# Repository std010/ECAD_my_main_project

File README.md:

# ECAD_my_main_project

Составлена и разведена принципиальная схема Модуля для очувствления протеза

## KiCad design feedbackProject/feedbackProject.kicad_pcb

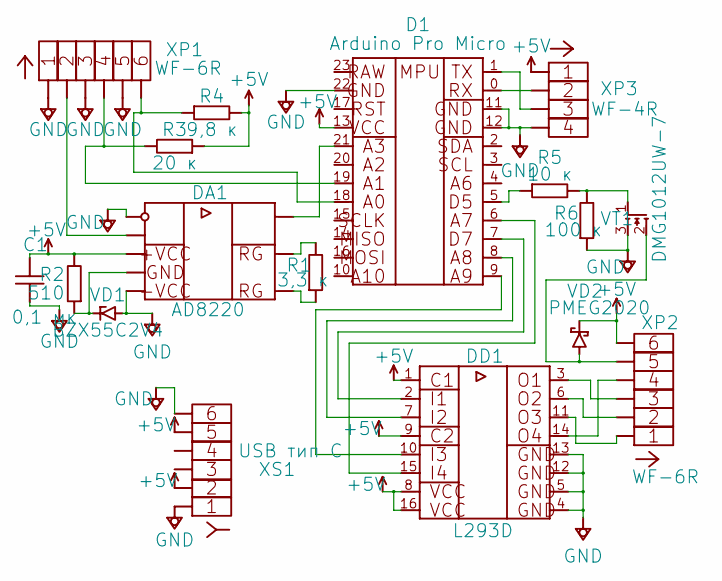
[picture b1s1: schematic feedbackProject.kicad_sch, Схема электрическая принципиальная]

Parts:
C1: 0,1 мк; capacitor_0805_Most_Density
D1: Arduino Pro Micro; proMicroSMD
DA1: AD8220; MSOP-8
DD1: L293D; PowerDIP-16
R1: 3,3 к; resistor_0805_Most_Density
R2: 510; resistor_0805_Most_Density
R3: 20 к; resistor_0805_Most_Density
R4: 9,8 к; resistor_0805_Most_Density
R5: 10 к; resistor_0805_Most_Density
R6: 100 к; resistor_0805_Most_Density
VD1: BZX55C2V4; diode_SOD-80C_Most_Density
VD2: PMEG2020; diode_SOD-323_Most_Density
VT1: DMG1012UW-7; transistor-SOT-323
XP1, XP2: WF-6R
XP3: WF-4R
XS1: USB тип C; USB-Type-C-4125-GF-A-0190

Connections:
+5V: C1.2, D1.13, DA1.8, DD1.1, DD1.8, DD1.9, DD1.16, R2.2, R3.1, R4.2, VD2.C, XP2.6, XP3.1, XS1.2, XS1.5
GND: C1.1, D1.11, D1.12, D1.22, DA1.1, DA1.5, DD1.4, DD1.5, DD1.12, DD1.13, R6.1, VD1.A, VT1.3, XP1.1, XP1.3, XP1.5, XP3.4, XS1.1, XS1.6
unnamed: D1.0, XP3.2
unnamed: D1.1, XP3.3
unnamed: D1.5, R5.1
unnamed: D1.6, DD1.15
unnamed: D1.7, DD1.2
unnamed: D1.8, DD1.7
unnamed: D1.9, DD1.10
unnamed: D1.18, R4.1, XP1.6
unnamed: D1.19, R3.2, XP1.4
unnamed: D1.21, DA1.7
unnamed: DA1.2, R1.2
unnamed: DA1.3, R1.1
unnamed: DA1.4, XP1.2
unnamed: DA1.6, R2.1, VD1.C
unnamed: DD1.3, XP2.3
unnamed: DD1.6, XP2.2
unnamed: DD1.11, XP2.1
unnamed: DD1.14, XP2.4
unnamed: R5.2, R6.2, VT1.1
unnamed: VD2.A, VT1.2, XP2.5

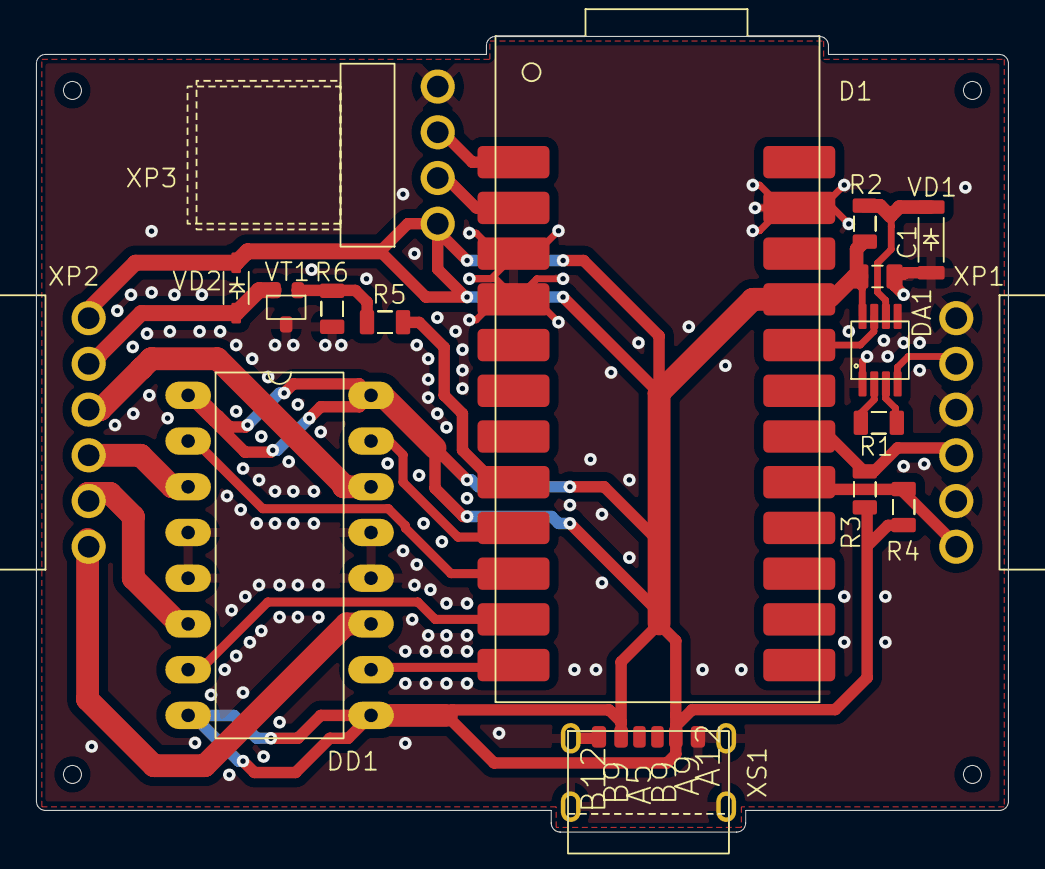
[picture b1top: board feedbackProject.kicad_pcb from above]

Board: 2 copper layers, 54.0 x 44.2 mm, 17 parts (0 on the bottom side), 22 nets.

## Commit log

2025-09-11 adding lib repo
2025-10-12 another check
2025-10-19 library update check
2025-10-20 library update check of adding Arduino pro micro footprint + minor fix in schematic
2025-10-20 library 2nd update check of adding Arduino pro micro footprint in main
2025-10-26 some fixes + PCB
2025-10-31 some fixes in PCB + readme
2025-10-31 lib update
